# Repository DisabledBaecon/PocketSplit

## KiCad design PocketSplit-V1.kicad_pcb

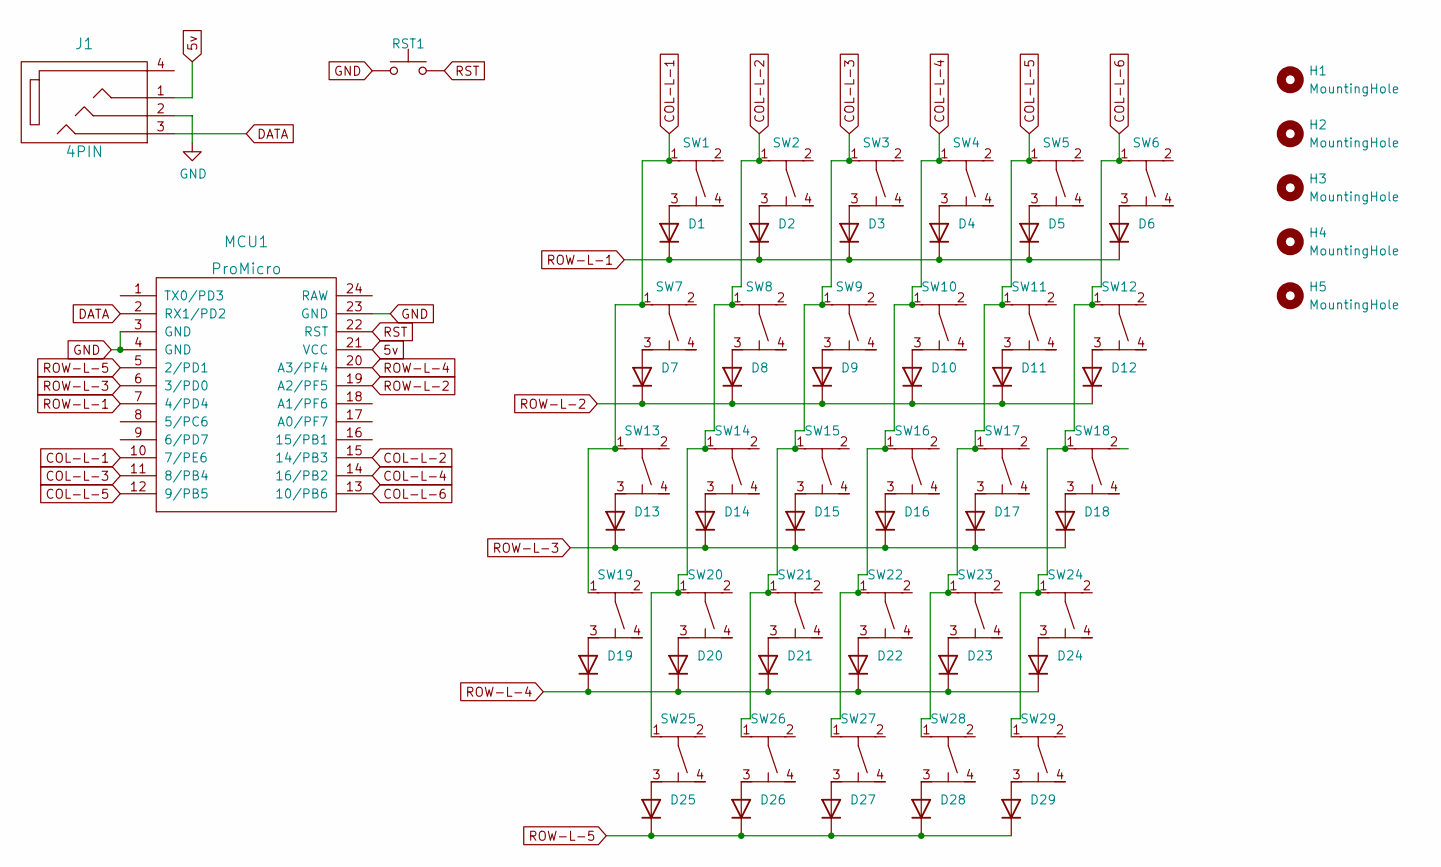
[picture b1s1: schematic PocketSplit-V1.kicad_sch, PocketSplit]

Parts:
D1, D2, D3, D4, D5, D6, D7, D8, D9, D10, D11, D12, D13, D14, D15, D16, D17, D18, D19, D20, D21, D22, D23, D24, D25, D26, D27, D28, D29: D; Diode_TH_SOD123_Edited
H1, H2, H3, H4, H5: MountingHole; MountingHole_2.2mm_M2
J1: 4PIN; MJ-4PP-9
MCU1: ProMicro; ProMicro_rev2
RST1: SW_Push; TACT_SWITCH_TVBP06
SW1, SW2, SW3, SW4, SW5, SW6, SW7, SW8, SW9, SW10, SW11, SW12, SW13, SW14, SW15, SW16, SW17, SW18, SW19, SW20, SW21, SW22, SW23, SW24, SW25, SW26, SW27, SW28, SW29: SW_THT_6x6; Switch_THT_6x6x8.5

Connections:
5v: J1.1, MCU1.21 (VCC)
COL-L-1: MCU1.10 (7/PE6), SW1.1, SW7.1, SW13.1, SW19.1
COL-L-2: MCU1.15 (14/PB3), SW2.1, SW8.1, SW14.1, SW20.1, SW25.1
COL-L-3: MCU1.11 (8/PB4), SW3.1, SW9.1, SW15.1, SW21.1, SW26.1
COL-L-4: MCU1.14 (16/PB2), SW4.1, SW10.1, SW16.1, SW22.1, SW27.1
COL-L-5: MCU1.12 (9/PB5), SW5.1, SW11.1, SW17.1, SW23.1, SW28.1
COL-L-6: MCU1.13 (10/PB6), SW6.1, SW12.1, SW18.1, SW24.1, SW29.1
DATA: J1.3, MCU1.2 (RX1/PD2)
GND: J1.2, MCU1.3 (GND), MCU1.4 (GND), MCU1.23 (GND), RST1.1
unnamed: D1.2 (A), SW1.3
unnamed: D2.2 (A), SW2.3
unnamed: D3.2 (A), SW3.3
unnamed: D4.2 (A), SW4.3
unnamed: D5.2 (A), SW5.3
unnamed: D6.2 (A), SW6.3
unnamed: D7.2 (A), SW7.3
unnamed: D8.2 (A), SW8.3
unnamed: D9.2 (A), SW9.3
unnamed: D10.2 (A), SW10.3
unnamed: D11.2 (A), SW11.3
unnamed: D12.2 (A), SW12.3
unnamed: D13.2 (A), SW13.3
unnamed: D14.2 (A), SW14.3
unnamed: D15.2 (A), SW15.3
unnamed: D16.2 (A), SW16.3
unnamed: D17.2 (A), SW17.3
unnamed: D18.2 (A), SW18.3
unnamed: D19.2 (A), SW19.3
unnamed: D20.2 (A), SW20.3
unnamed: D21.2 (A), SW21.3
unnamed: D22.2 (A), SW22.3
unnamed: D23.2 (A), SW23.3
unnamed: D24.2 (A), SW24.3
unnamed: D25.2 (A), SW25.3
unnamed: D26.2 (A), SW26.3
unnamed: D27.2 (A), SW27.3
unnamed: D28.2 (A), SW28.3
unnamed: D29.2 (A), SW29.3
ROW-L-1: D1.1 (K), D2.1 (K), D3.1 (K), D4.1 (K), D5.1 (K), D6.1 (K), MCU1.7 (4/PD4)
ROW-L-2: D7.1 (K), D8.1 (K), D9.1 (K), D10.1 (K), D11.1 (K), D12.1 (K), MCU1.19 (A2/PF5)
ROW-L-3: D13.1 (K), D14.1 (K), D15.1 (K), D16.1 (K), D17.1 (K), D18.1 (K), MCU1.6 (3/PD0)
ROW-L-4: D19.1 (K), D20.1 (K), D21.1 (K), D22.1 (K), D23.1 (K), D24.1 (K), MCU1.20 (A3/PF4)
ROW-L-5: D25.1 (K), D26.1 (K), D27.1 (K), D28.1 (K), D29.1 (K), MCU1.5 (2/PD1)
RST: MCU1.22 (RST), RST1.2

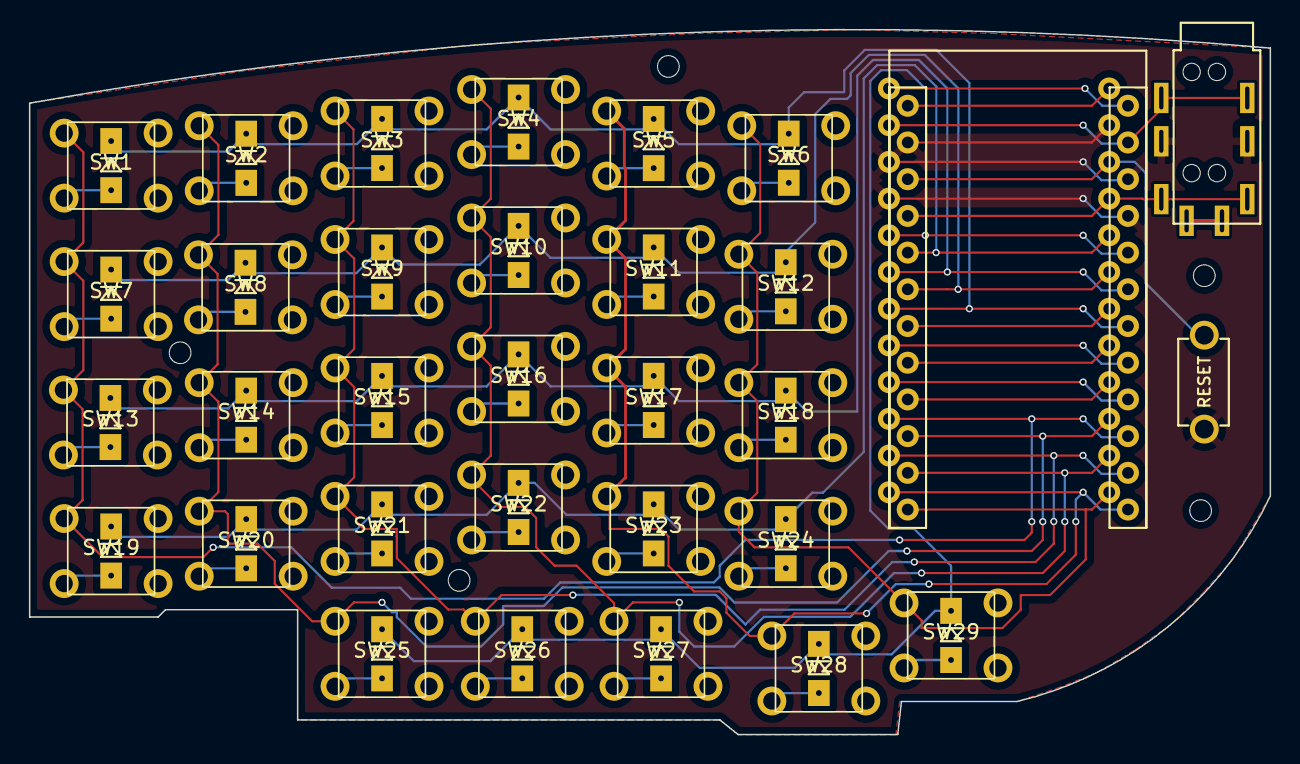
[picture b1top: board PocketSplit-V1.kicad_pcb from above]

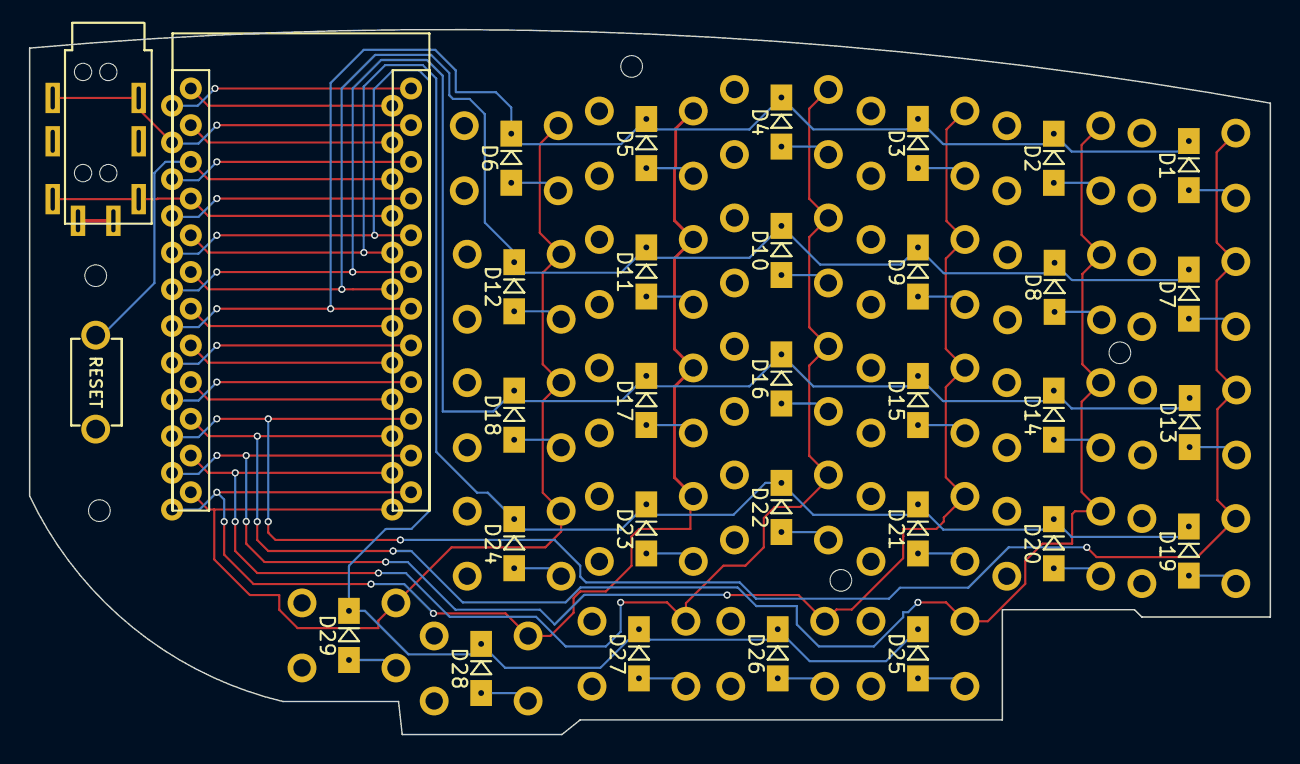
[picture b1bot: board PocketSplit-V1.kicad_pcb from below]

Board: 2 copper layers, 85.9 x 48.8 mm, 66 parts (29 on the bottom side), 44 nets.

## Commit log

2022-12-16 Added Gerbers
2022-12-16 No idea
2022-12-16 PCB updates
2022-12-16 Added M1.4 mounting holes
2022-12-16 Not sure
2022-12-16 Added things
